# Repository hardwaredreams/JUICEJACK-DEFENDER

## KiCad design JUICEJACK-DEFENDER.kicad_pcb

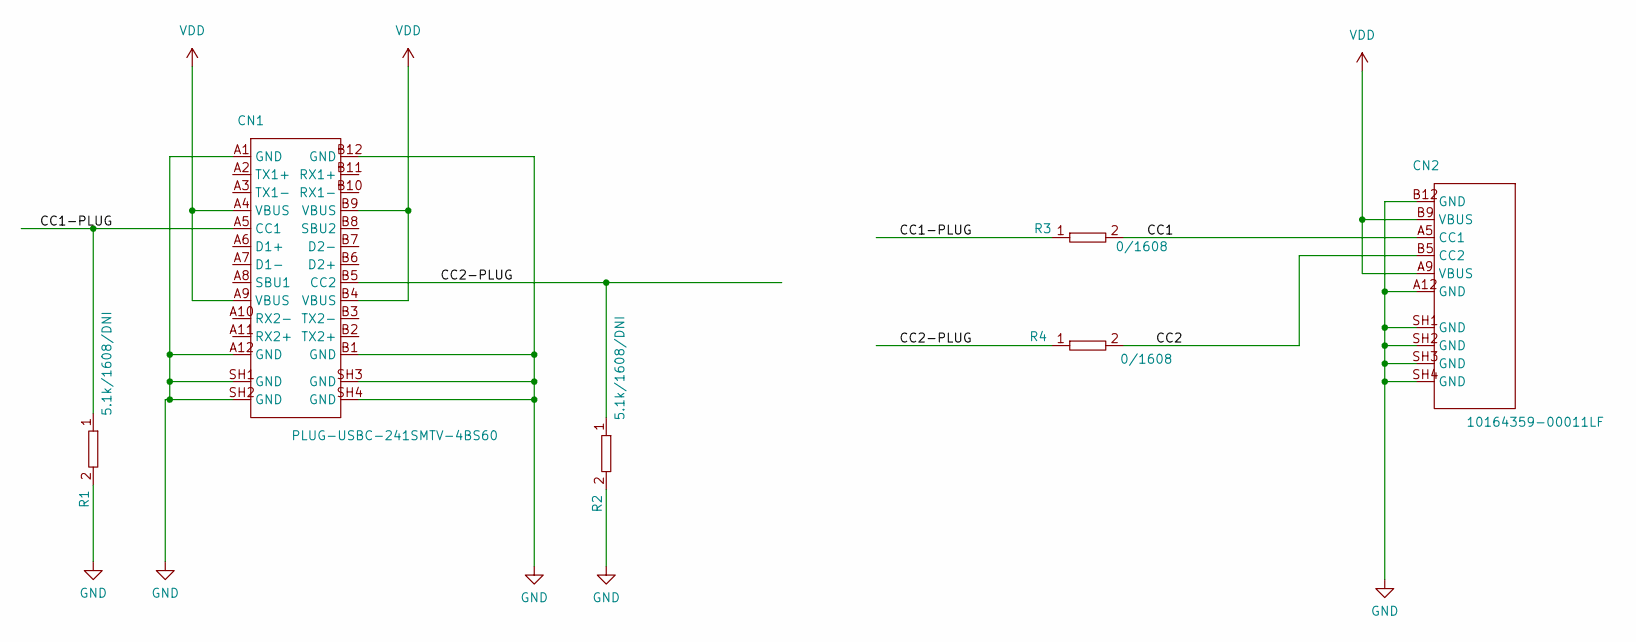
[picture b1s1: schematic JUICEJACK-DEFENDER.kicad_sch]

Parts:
CN1: PLUG-USBC-241SMTV-4BS60
CN2: 10164359-00011LF; AMPHENOL_10164359-00011LF
R1, R2: 5.1k/1608/DNI; generic-r1608-DNI
R3, R4: 0/1608; generic-r1608

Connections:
/CC1: CN2.A5 (CC1), R3.2
/CC1-PLUG: CN1.A5 (CC1), R1.1, R3.1
/CC2: CN2.B5 (CC2), R4.2
/CC2-PLUG: CN1.B5 (CC2), R2.1, R4.1
GND: CN1.A1 (GND), CN1.A12 (GND), CN1.B1 (GND), CN1.B12 (GND), CN1.SH1 (GND), CN1.SH2 (GND), CN1.SH3 (GND), CN1.SH4 (GND), CN2.A12 (GND), CN2.B12 (GND), CN2.SH1 (GND), CN2.SH2 (GND), CN2.SH3 (GND), CN2.SH4 (GND), R1.2, R2.2
VDD: CN1.A4 (VBUS), CN1.A9 (VBUS), CN1.B4 (VBUS), CN1.B9 (VBUS), CN2.A9 (VBUS), CN2.B9 (VBUS)

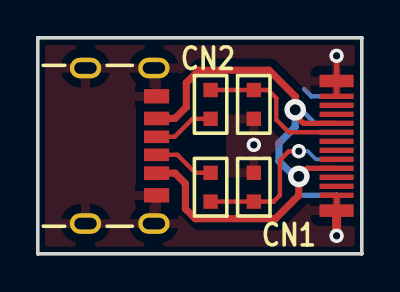
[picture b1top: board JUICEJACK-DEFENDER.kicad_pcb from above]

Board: 2 copper layers, 18.0 x 12.0 mm, 6 parts (0 on the bottom side), 6 nets.

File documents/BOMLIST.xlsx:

No. | リファレンス | 品名 | 型番 | 仕様 | 数量 | 実装 | 販売店等 | 備考
1 | CN1 | USB Type-C プラグ | PLUG-USBC-241SMTV-4BS60 | USB Type-C プラグ | 1 | 実装 | Digikey, Mouserほか | 相当品の場合あり
2 | CN2 | USB Type-Cレセプタ | 10164359-00011LF | USB Type-C レセプタ | 1 | 実装 | Digikey, Mouserほか | 相当品の場合あり
3 | R1,R2 | チップ抵抗 | ERJ-3EKF5101V | 5.1kΩ/1608/0.1W | 2 | 未実装 | Digikey, Mouserほか | 相当品の場合あり
4 | R3,R4 | チップ抵抗 | ERJ-3GEY0R00V | 0Ω ジャンパ抵抗/1608/0.1W | 2 | 実装 | Digikey, Mouserほか | 相当品の場合あり
5 | PCB | JUICEJACK-DEFENDER基板 |  |  | 1 | 実装 | オーダーメイド品 | 専用基板

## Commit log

2024-06-07 1st commit
2024-06-10 deleted file
2024-06-13 レセプタ側 型番修正
2024-06-13 PCBレイアウト図、ガーバーデータ追加
2024-06-19 3Dモデルの更新
2024-06-19 Webページ用ファイルの追加
2024-07-10 bomlistの追加
